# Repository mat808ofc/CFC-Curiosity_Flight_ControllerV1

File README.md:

# CFC (Curiosity's Flight Controller)

### About

This is a flight controller with USB-C, a Micro-SD card reader, a battery charger, servos, a pressure sensor, a IMU, a GNSS Module and voltage sensing via ADC. It was originally designed for model rockets but it can be used for planes too. I took inspiration from the @NotARoomba SFC guide, but designed it myself and this is my own creation.

### INSPIRATION:

This is my second project and first stasis project. Since I want to follow aerospace engineering, i chose to build a flight controller. I followed the @NotARoomba guide and built it from scratch. I added a GNSS Module for auto pilot and Voltage Sensing via ADC to know when the battery is getting low. I want to use this in my custom built RC plane. I really liked building everything although some things were a real pain.

### CHALLENGES:

My biggest challenge was routing the PCB, when I routed it for the first time the board was way too big to fit on the plane and way too expensive. So after that I significantly reduced the board size and made it the smallest it can get and the cheapest. In between that, I had to change a lot of pins and inputs in STM32CubeMX so that the routing wouldn't be an absolute mess, and that took a really long time and absolutely drained my patience and mental power.

### BOM:
| Name            | Purpose                      | Cost (USD) | Qty | Total (USD) | Link                         | Distributor |
|-----------------|-----------------------------|------------|-----|-------------|------------------------------|-------------|
| PCBA (1 board)  | The actual flight controller | $140       | 1   | $140        | https://www.elecrow.com/     | Elecrow     |

Total estimated cost: $140

### Extras:

This project does not need a case or anything 3D printed or designed, it will be inside a RC plane.
If you have any questions, DM me on slack: Mateus (mateus.flecha808)

## Schematic

### USB-C & Crystals

### Decoupling, Buttons & Servos

### Battery Charger & STM32

### Pressure Sensor & Micro-SD

### Power & GNSS

### IMU

### All

---

## PCB

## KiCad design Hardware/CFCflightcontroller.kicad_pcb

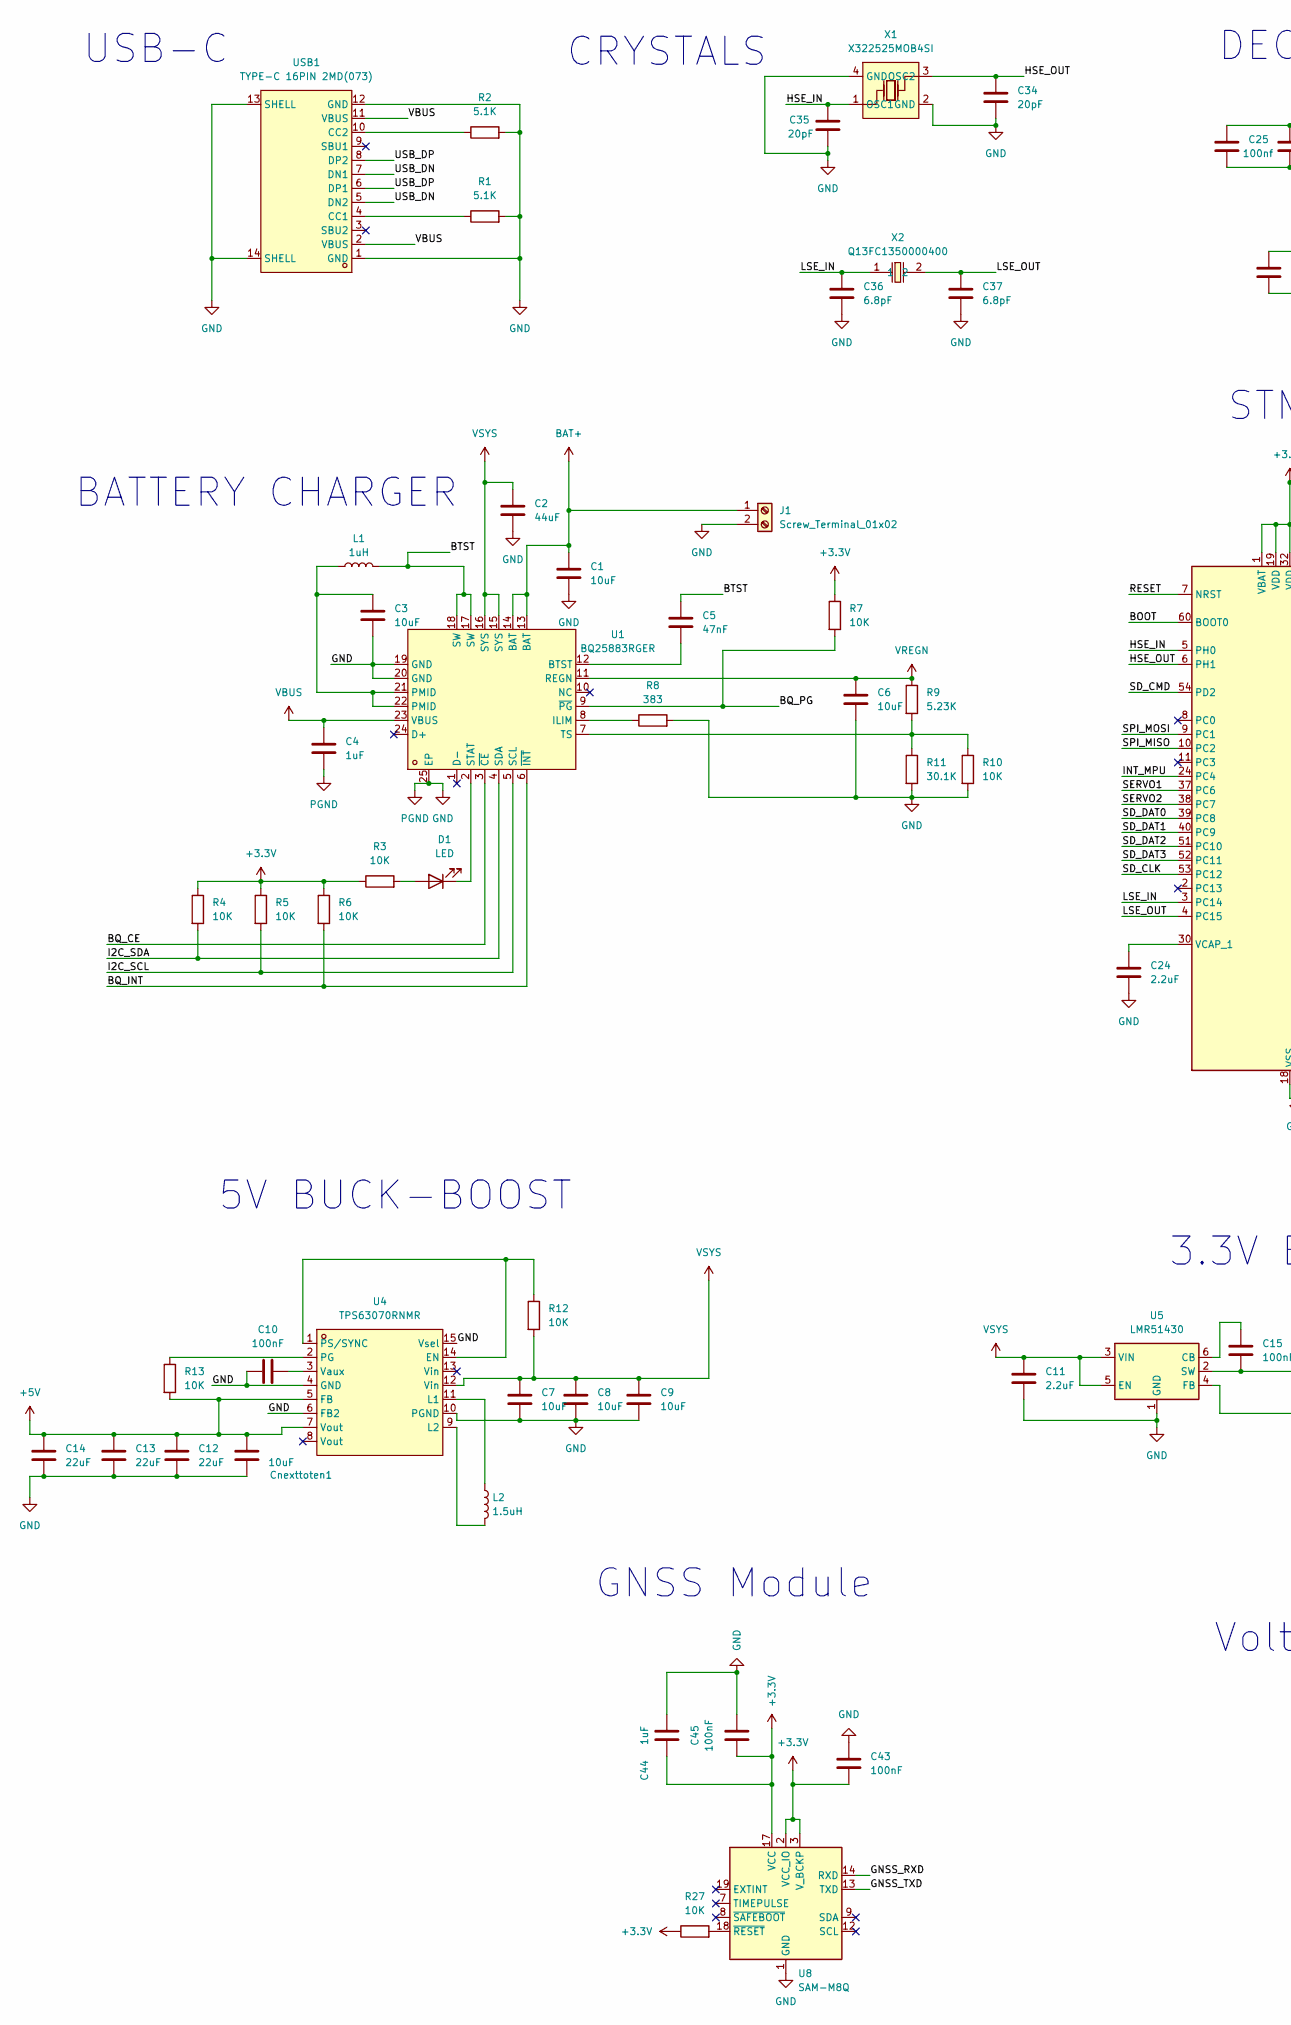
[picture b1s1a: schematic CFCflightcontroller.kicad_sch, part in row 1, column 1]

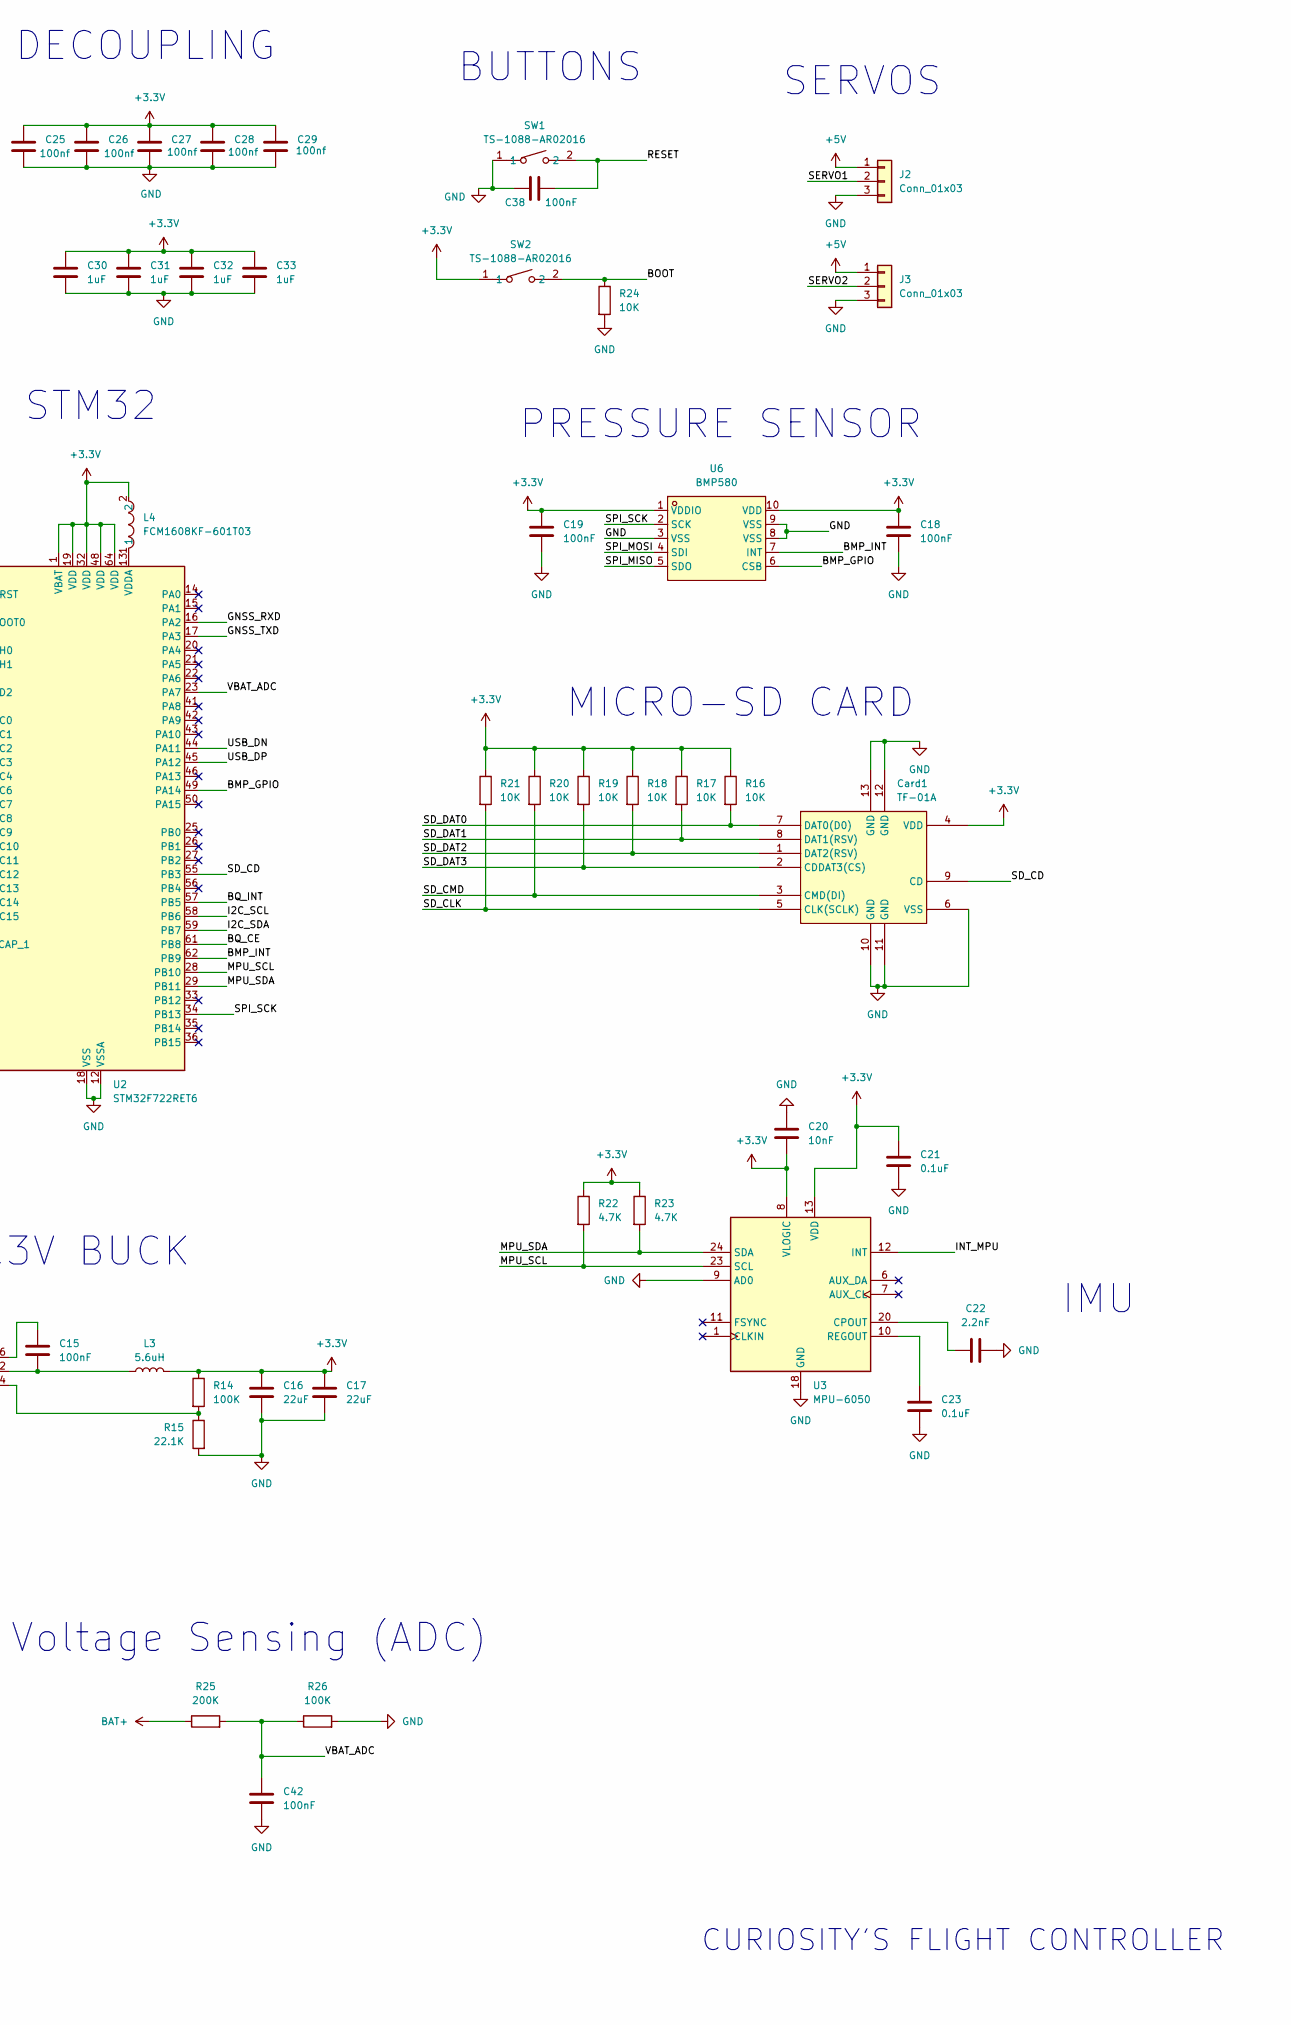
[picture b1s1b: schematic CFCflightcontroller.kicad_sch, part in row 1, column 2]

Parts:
C1, C3, C6, C7, C8, C9: 10uF; C_0805_2012Metric
C2: 44uF; C_0805_2012Metric
C4: 1uF; C_0805_2012Metric
C5: 47nF; C_0805_2012Metric
C10, C15, C18, C19, C38, C42, C43, C45: 100nF; C_0805_2012Metric
C11, C24: 2.2uF; C_0402_1005Metric
C12, C13, C14, C16, C17: 22uF; C_0805_2012Metric
C20: 10nF; C_0805_2012Metric
C21, C23: 0.1uF; C_0402_1005Metric
C22: 2.2nF; C_0402_1005Metric
C25, C26, C27, C28, C29: 100nf; C_0805_2012Metric
C30, C31, C32, C33, C44: 1uF; C_0402_1005Metric
C34, C35: 20pF; C_0805_2012Metric
C36, C37: 6.8pF; C_0402_1005Metric
Card1: TF-01A; TF-SMD_TF-01A; LCSC Part C91145
Cnexttoten1: 10uF; C_0805_2012Metric
D1: LED; LED_0402_1005Metric
J1: Screw_Terminal_01x02; TerminalBlock_Xinya_XY308-2.54-2P_1x02_P2.54mm_Horizontal
J2, J3: Conn_01x03; PinHeader_1x03_P2.54mm_Vertical
L1: 1uH; L2520
L2: 1.5uH; IND-SMD_L4.0-W4.0-A
L3: 5.6uH; IND-SMD_L3.0-W3.0
L4: FCM1608KF-601T03; L0603; LCSC Part C141723
R1, R2: 5.1K; R_0402_1005Metric
R3, R4, R5, R6, R7, R10, R12, R13, R16, R17, R18, R19, R20, R21, R24, R27: 10K; R_0402_1005Metric
R8: 383; R_0402_1005Metric
R9: 5.23K; R_0402_1005Metric
R11: 30.1K; R_0402_1005Metric
R14: 100K; R_0402_1005Metric
R15: 22.1K; R_0402_1005Metric
R22, R23: 4.7K; R_0402_1005Metric
R25: 200K; R_0805_2012Metric
R26: 100K; R_0805_2012Metric
SW1, SW2: TS-1088-AR02016; SW-SMD_L3.9-W3.0-P4.45; LCSC Part C720477
U1: BQ25883RGER; VFQFPN-24_L4.0-W4.0-P0.50-BL-EP2.8; LCSC Part C544362
U2: STM32F722RET6; LQFP-64_10x10mm_P0.5mm
U3: MPU-6050; InvenSense_QFN-24_4x4mm_P0.5mm
U4: TPS63070RNMR; VQFN-15_L3.0-W2.5-P0.50-BL; LCSC Part C109322
U5: LMR51430; SOT-23-6
U6: BMP580; LGA-10_L2.0-W2.0-P0.50-TL_BMP580; LCSC Part C22391138
U8: SAM-M8Q; ublox_SAM-M8Q
USB1: TYPE-C 16PIN 2MD(073); USB-C-SMD_TYPE-C-6PIN-2MD-073; LCSC Part C2765186
X1: X322525MOB4SI; CRYSTAL-SMD_4P-L3.2-W2.5-BL; LCSC Part C9006
X2: Q13FC1350000400; FC-135R_L3.2-W1.5; LCSC Part C32346

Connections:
+3.3V: C16.1, C17.1, C18.1, C19.1, C20.2, C21.1, C25.1, C26.1, C27.1, C28.1, C29.1, C30.1, C31.1, C32.1, C33.1, C43.1, C44.1, C45.1, Card1.4 (VDD), L3.2, L4.2, R3.1, R4.1, R5.1, R6.1, R7.1, R14.1, R16.1, R17.1, R18.1, R19.1, R20.1, R21.1, R22.1, R23.1, R27.1, SW2.1, U2.1 (VBAT), U2.19 (VDD), U2.32 (VDD), U2.48 (VDD), U2.64 (VDD), U3.8 (VLOGIC), U3.13 (VDD), U6.1 (VDDIO), U6.10 (VDD), U8.2 (VCC_IO), U8.3 (V_BCKP), U8.17 (VCC)
+5V: C12.1, C13.1, C14.1, Cnexttoten1.1, J2.1, J3.1, R13.2, U4.5 (FB), U4.7 (Vout)
/BMP_GPIO: U2.49 (PA14), U6.6 (CSB)
/BMP_INT: U2.62 (PB9), U6.7 (INT)
/BOOT: R24.1, SW2.2, U2.60 (BOOT0)
/BQ_CE: U1.3 (~CE), U2.61 (PB8)
/BQ_INT: R6.2, U1.6 (~INT), U2.57 (PB5)
/BQ_PG: R7.2, U1.9 (~PG)
/BTST: C5.1, L1.2, U1.17 (SW), U1.18 (SW)
/GNSS_RXD: U2.16 (PA2), U8.14 (RXD)
/GNSS_TXD: U2.17 (PA3), U8.13 (TXD)
/HSE_IN: C35.1, U2.5 (PH0), X1.1 (OSC1)
/HSE_OUT: C34.1, U2.6 (PH1), X1.3 (OSC2)
/I2C_SCL: R5.2, U1.5 (SCL), U2.58 (PB6)
/I2C_SDA: R4.2, U1.4 (SDA), U2.59 (PB7)
/INT_MPU: U2.24 (PC4), U3.12 (INT)
/LSE_IN: C36.1, U2.3 (PC14), X2.1
/LSE_OUT: C37.1, U2.4 (PC15), X2.2
/MPU_SCL: R22.2, U2.28 (PB10), U3.23 (SCL)
/MPU_SDA: R23.2, U2.29 (PB11), U3.24 (SDA)
/RESET: C38.2, SW1.2, U2.7 (NRST)
/SD_CD: Card1.9 (CD), U2.55 (PB3)
/SD_CLK: Card1.5 (CLK(SCLK)), R21.2, U2.53 (PC12)
/SD_CMD: Card1.3 (CMD(DI)), R20.2, U2.54 (PD2)
/SD_DAT0: Card1.7 (DAT0(D0)), R16.2, U2.39 (PC8)
/SD_DAT1: Card1.8 (DAT1(RSV)), R17.2, U2.40 (PC9)
/SD_DAT2: Card1.1 (DAT2(RSV)), R18.2, U2.51 (PC10)
/SD_DAT3: Card1.2 (CDDAT3(CS)), R19.2, U2.52 (PC11)
/SERVO1: J2.2, U2.37 (PC6)
/SERVO2: J3.2, U2.38 (PC7)
/SPI_MISO: U2.10 (PC2), U6.5 (SDO)
/SPI_MOSI: U2.9 (PC1), U6.4 (SDI)
/SPI_SCK: U2.34 (PB13), U6.2 (SCK)
/USB_DN: U2.44 (PA11), USB1.5 (DN2), USB1.7 (DN1)
/USB_DP: U2.45 (PA12), USB1.6 (DP1), USB1.8 (DP2)
/VBAT_ADC: C42.1, R25.2, R26.1, U2.23 (PA7)
BAT+: C1.1, J1.1, R25.1, U1.13 (BAT), U1.14 (BAT)
GND: C1.2, C2.2, C3.2, C4.2, C6.2, C7.2, C8.2, C9.2, C10.1, C11.2, C12.2, C13.2, C14.2, C16.2, C17.2, C18.2, C19.2, C20.1, C21.2, C22.2, C23.2, C24.2, C25.2, C26.2, C27.2, C28.2, C29.2, C30.2, C31.2, C32.2, C33.2, C34.2, C35.2, C36.2, C37.2, C38.1, C42.2, C43.2, C44.2, C45.2, Card1.6 (VSS), Card1.10 (GND), Card1.11 (GND), Card1.12 (GND), Card1.13 (GND), Cnexttoten1.2, J1.2, J2.3, J3.3, R1.2, R2.2, R8.2, R10.2, R11.2, R15.2, R24.2, R26.2, SW1.1, U1.19 (GND), U1.20 (GND), U1.25 (EP), U2.12 (VSSA), U2.18 (VSS), U2.31 (VSS), U2.47 (VSS), U2.63 (VSS), U3.9 (AD0), U3.18 (GND), U4.4 (GND), U4.6 (FB2), U4.10 (PGND), U4.15 (Vsel), U5.1 (GND), U6.3 (VSS), U6.8 (VSS), U6.9 (VSS), U8.1 (GND), U8.4 (GND), U8.5 (GND), U8.6 (GND), U8.10 (GND), U8.11 (GND), U8.15 (GND), U8.16 (GND), U8.20 (GND), USB1.1 (GND), USB1.12 (GND), USB1.13 (SHELL), USB1.14 (SHELL), X1.2 (GND), X1.4 (GND)
unnamed: C3.1, L1.1, U1.21 (PMID), U1.22 (PMID)
unnamed: D1.2 (A), R3.2
unnamed: D1.1 (K), U1.2 (STAT)
unnamed: C5.2, U1.12 (BTST)
unnamed: R8.1, U1.8 (ILIM)
unnamed: R9.2, R10.1, R11.1, U1.7 (TS)
unnamed: C24.1, U2.30 (VCAP_1)
unnamed: L4.1, U2.13 (VDDA)
unnamed: C22.1, U3.20 (CPOUT)
unnamed: C23.1, U3.10 (REGOUT)
unnamed: R12.1, U4.1 (PS/SYNC), U4.14 (EN)
unnamed: L2.1, U4.11 (L1)
unnamed: L2.2, U4.9 (L2)
unnamed: R13.1, U4.2 (PG)
unnamed: C10.2, U4.3 (Vaux)
unnamed: C15.1, U5.6 (CB)
unnamed: R14.2, R15.1, U5.4 (FB)
unnamed: C15.2, L3.1, U5.2 (SW)
unnamed: R27.2, U8.18 (~RESET)
unnamed: R1.1, USB1.4 (CC1)
unnamed: R2.1, USB1.10 (CC2)
VBUS: C4.1, U1.23 (VBUS), USB1.2 (VBUS), USB1.11 (VBUS)
VREGN: C6.1, R9.1, U1.11 (REGN)
VSYS: C2.1, C7.1, C8.1, C9.1, C11.1, R12.2, U1.15 (SYS), U1.16 (SYS), U4.12 (Vin), U5.3 (VIN), U5.5 (EN)

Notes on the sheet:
DECOUPLING
CURIOSITY'S FLIGHT CONTROLLER
5V BUCK-BOOST
MICRO-SD CARD
CRYSTALS
USB-C
BUTTONS
IMU
Voltage Sensing (ADC)
PRESSURE SENSOR
BATTERY CHARGER
SERVOS
GNSS Module
3.3V BUCK
STM32

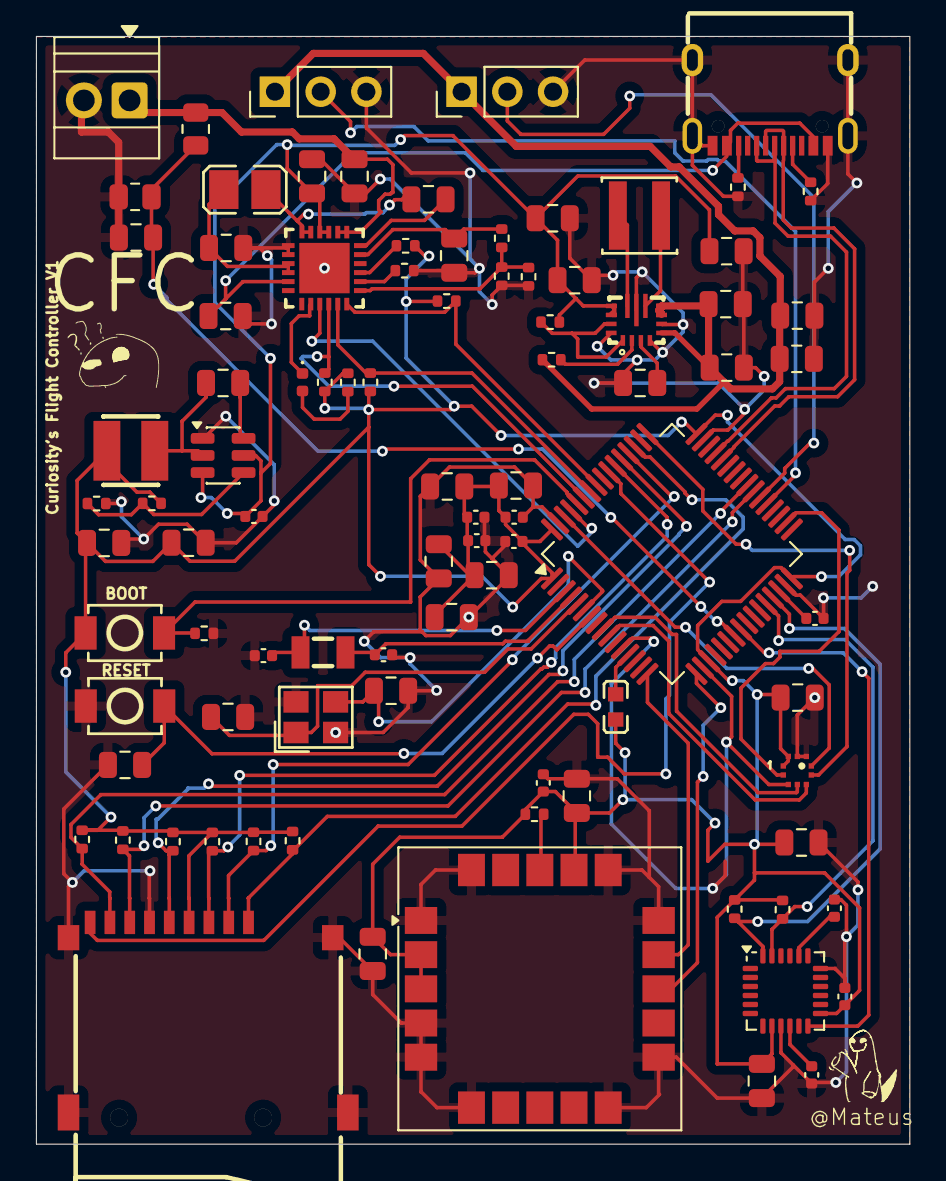
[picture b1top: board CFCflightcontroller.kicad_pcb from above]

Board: 2 copper layers, 48.5 x 61.5 mm, 91 parts (0 on the bottom side), 62 nets.

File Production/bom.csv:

Designator,Footprint,Quantity,Value,LCSC Part #
"C1, C3, C6, C7, C8, C9, CNEXTTOTEN1",0805,7,10uF,
"C10, C15, C18, C19, C25, C26, C27, C28, C29, C38, C42, C43, C45",0805,13,100nF,
"C11, C24",0402,2,2.2uF,
"C12, C13, C14, C16, C17",0805,5,22uF,
C2,0805,1,44uF,
C20,0805,1,10nF,
"C21, C23",0402,2,0.1uF,
C22,0402,1,2.2nF,
"C30, C31, C32, C33, C44",0402,5,1uF,
"C34, C35",0805,2,20pF,
"C36, C37",0402,2,6.8pF,
C4,0805,1,1uF,
C5,0805,1,47nF,
CARD1,TF-SMD_TF-01A,1,TF-01A,C91145
D1,0402,1,LED,
J1,TerminalBlock_Xinya_XY308-2.54-2P_1x02_P2.54mm_Horizontal,1,Screw_Terminal_01x02,
"J2, J3",PinHeader_1x03_P2.54mm_Vertical,2,Conn_01x03,
L1,L2520,1,1uH,
L2,IND-SMD_L4.0-W4.0-A,1,1.5uH,
L3,IND-SMD_L3.0-W3.0,1,5.6uH,
L4,L0603,1,FCM1608KF-601T03,C141723
"R1, R2",0402,2,5.1K,
"R10, R12, R13, R16, R17, R18, R19, R20, R21, R24, R27, R3, R4, R5, R6, R7",0402,16,10K,
R11,0402,1,30.1K,
R14,0402,1,100K,
R15,0402,1,22.1K,
"R22, R23",0402,2,4.7K,
R25,0805,1,200K,
R26,0805,1,100K,
R8,0402,1,383,
R9,0402,1,5.23K,
"SW1, SW2",SW-SMD_L3.9-W3.0-P4.45,2,TS-1088-AR02016,C720477
U1,VFQFPN-24_L4.0-W4.0-P0.50-BL-EP2.8,1,BQ25883RGER,C544362
U2,LQFP-64_10x10mm_P0.5mm,1,STM32F722RET6,
U3,InvenSense_QFN-24_4x4mm_P0.5mm,1,MPU-6050,
U4,VQFN-15_L3.0-W2.5-P0.50-BL,1,TPS63070RNMR,C109322
U5,SOT-23-6,1,LMR51430,
U6,LGA-10_L2.0-W2.0-P0.50-TL_BMP580,1,BMP580,C22391138
U8,ublox_SAM-M8Q,1,SAM-M8Q,
USB1,USB-C-SMD_TYPE-C-6PIN-2MD-073,1,TYPE-C 16PIN 2MD(073),C2765186
X1,CRYSTAL-SMD_4P-L3.2-W2.5-BL,1,X322525MOB4SI,C9006
X2,FC-135R_L3.2-W1.5,1,Q13FC1350000400,C32346

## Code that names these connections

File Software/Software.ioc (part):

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Mcu.Name=STM32F722R(C-E)Tx
Mcu.Package=LQFP64
Mcu.UserName=STM32F722RETx
PA11.Mode=Host_Only
PA11.Signal=USB_OTG_FS_DM
PA12.Mode=Host_Only
PA12.Signal=USB_OTG_FS_DP
PA14.Signal=GPIO_Output
PA2.Mode=Asynchronous
PA2.Signal=USART2_TX
PA3.Mode=Asynchronous
PA3.Signal=USART2_RX
PA7.Signal=ADCx_IN7
PB10.Mode=I2C
PB10.Signal=I2C2_SCL
PB11.Mode=I2C
PB11.Signal=I2C2_SDA
PB13.Mode=Full_Duplex_Master
PB13.Signal=SPI2_SCK
PB3.Signal=GPIO_Input
PB5.Signal=GPXTI5
PB6.Mode=I2C
PB6.Signal=I2C1_SCL
PB7.Mode=I2C
PB7.Signal=I2C1_SDA
PB8.Signal=GPIO_Output
PC1.Mode=Full_Duplex_Master
PC1.Signal=SPI2_MOSI
PC10.Mode=mmc_4_bits_Wide_bus
PC10.Signal=SDMMC1_D2
PC11.Mode=mmc_4_bits_Wide_bus
PC11.Signal=SDMMC1_D3
PC12.Mode=mmc_4_bits_Wide_bus
PC12.Signal=SDMMC1_CK
PC14-OSC32_IN.Mode=LSE-External-Oscillator
PC14-OSC32_IN.Signal=RCC_OSC32_IN
PC15-OSC32_OUT.Mode=LSE-External-Oscillator
PC15-OSC32_OUT.Signal=RCC_OSC32_OUT
PC2.Mode=Full_Duplex_Master
PC2.Signal=SPI2_MISO
PC4.Signal=GPXTI4
PC6.Signal=S_TIM3_CH1
PC7.Signal=S_TIM3_CH2
PC8.Mode=mmc_4_bits_Wide_bus
PC8.Signal=SDMMC1_D0
PC9.Mode=mmc_4_bits_Wide_bus
PC9.Signal=SDMMC1_D1
PD2.Mode=mmc_4_bits_Wide_bus
PD2.Signal=SDMMC1_CMD
PH0-OSC_IN.Mode=HSE-External-Oscillator
PH0-OSC_IN.Signal=RCC_OSC_IN
PH1-OSC_OUT.Mode=HSE-External-Oscillator
PH1-OSC_OUT.Signal=RCC_OSC_OUT
RCC.HSE_VALUE=25000000
board=custom

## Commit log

2026-03-13 Enhance README with project details and challenges
    Expanded README with project inspiration and challenges faced during development.
2026-03-13 Fix project title in README.md
    Corrected the project title formatting and added apostrophe.
2026-03-16 Enhance README with project details and images
    Added detailed project description, BOM, and images.
2026-03-17 Add note about unpredictable PCBA costs
    Added an important note regarding component costs and procurement uncertainties.
2026-03-21 Revise BOM and total cost in README
    Updated BOM with new pricing and supplier information.
